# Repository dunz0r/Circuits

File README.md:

My collection libs, schematics, pcbs
Some done by me, some done by others

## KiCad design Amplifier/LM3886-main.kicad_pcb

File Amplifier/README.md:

An LM3886-powered gain-clone-amp

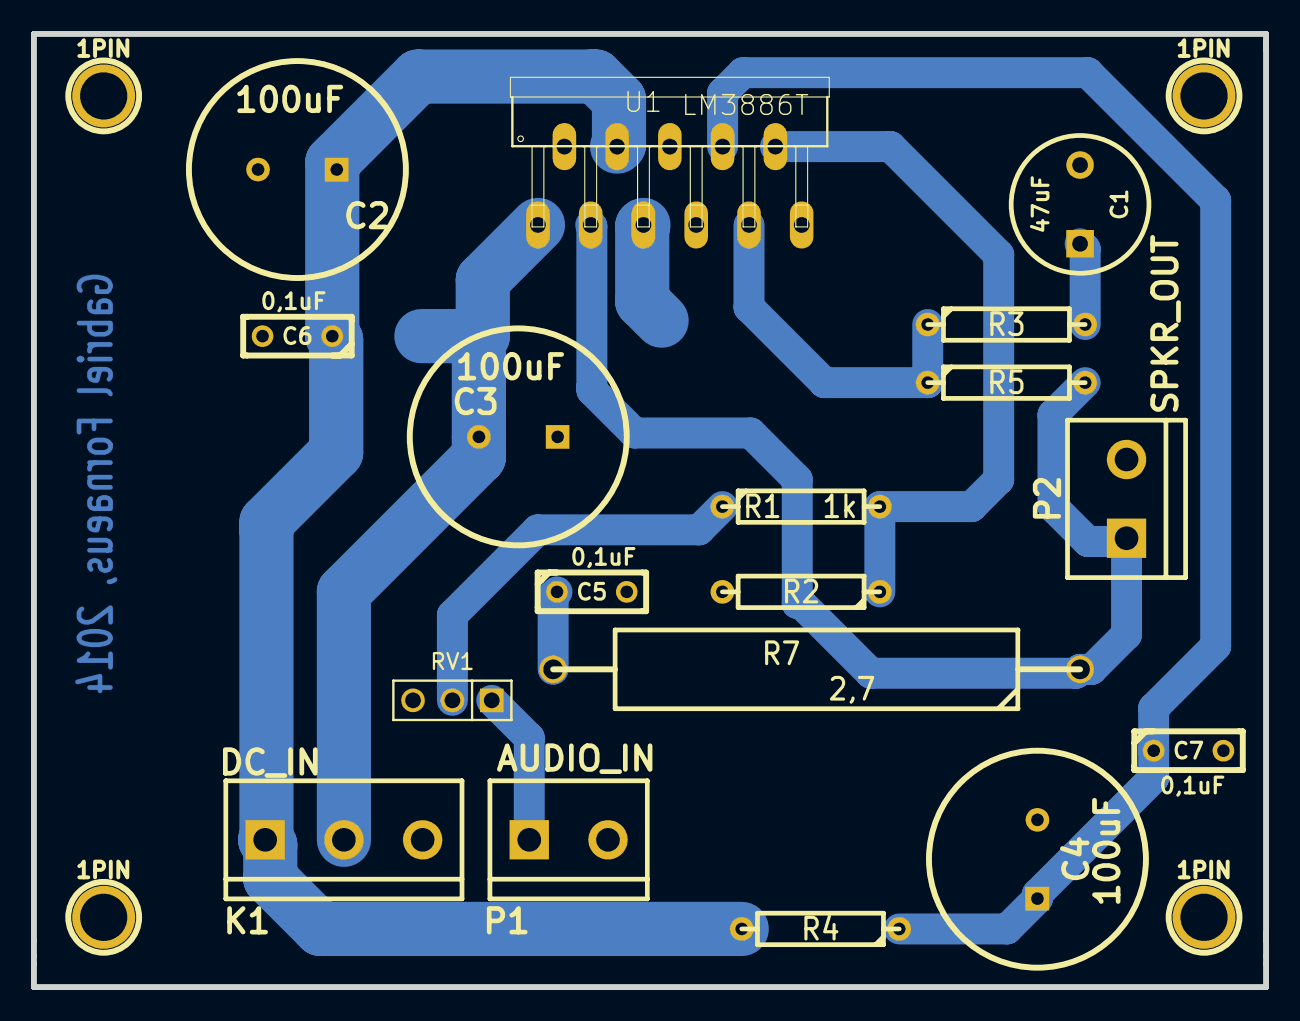
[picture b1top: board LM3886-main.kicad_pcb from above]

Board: 2 copper layers, 79.5 x 61.5 mm, 22 parts (0 on the bottom side), 11 nets.

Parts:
1PIN, 1PIN#2, 1PIN#3, 1PIN#4: P***; 1pin
C1: 47uF; C2V8
C2, C3, C4: 100uF; CP
C5, C6, C7: 0,1uF; C3
K1: DC_IN; bornier3
P1: AUDIO_IN; bornier2
P2: SPKR_OUT; bornier2
R1: 1k; R4
R2, R5: 22k; R4
R3: 680; R4
R4: 10k; R4
R7: 2,7; R8
RV1: 10k; PIN_ARRAY_3X1
U1: LM3886T; lmopamp-LM3886

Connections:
GND: C1.2, C2.1, C3.2, C4.1, C5.2, C6.2, C7.2, K1.3, P1.2, P2.2, R2.2, RV1.3, U1.7
unnamed: R1.2, R2.1, U1.10
unnamed: C1.1, R3.2
unnamed: C4.2, C7.1, R4.1, U1.8
unnamed: R1.1, RV1.2
unnamed: P1.1, RV1.1
unnamed: R3.1, R5.1, U1.9
unnamed: C5.1, R7.2
unnamed: P2.1, R5.2, R7.1, U1.3
VCC: C3.1, K1.2, U1.1, U1.5
VEE: C2.2, C6.1, K1.1, R4.2, U1.4

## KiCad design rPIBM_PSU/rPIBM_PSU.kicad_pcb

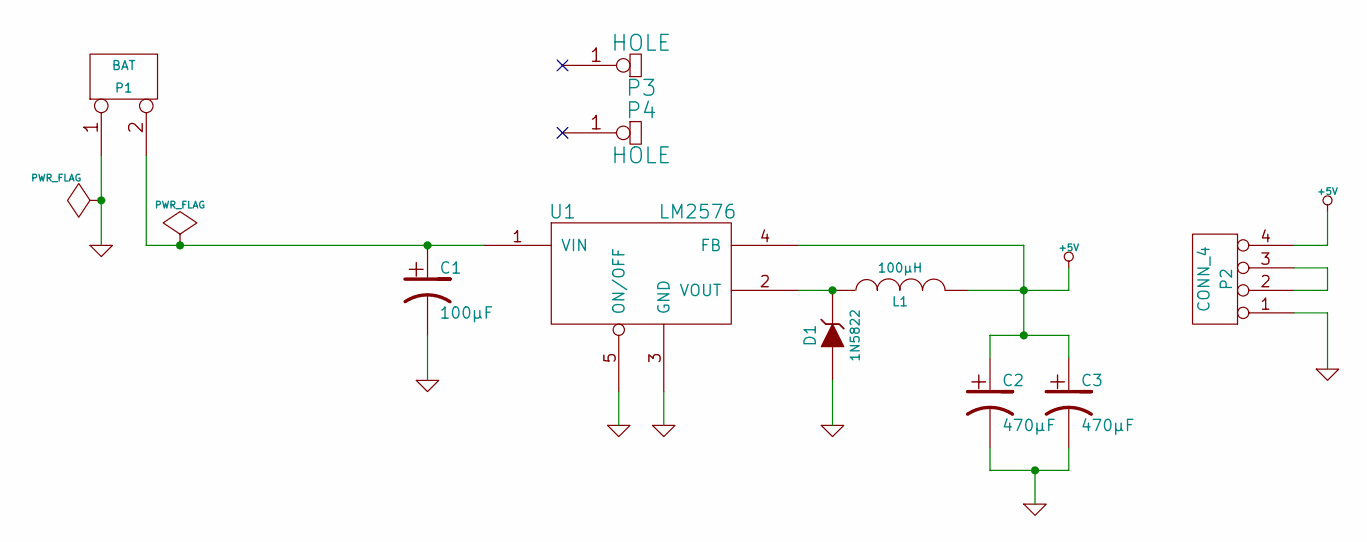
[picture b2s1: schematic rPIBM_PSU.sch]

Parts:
C1: 100µF
C2, C3: 470µF
D1: 1N5822
L1: 100µH
P1: BAT
P2: CONN_4
P3, P4: HOLE
U1: LM2576

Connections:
+5V: C2.1, C3.1, L1.2, P2.4, U1.4 (FB)
GND: C1.2, C2.2, C3.2, D1.1 (A), P1.1, P2.1, U1.3 (GND), U1.5 (ON/OFF)
unnamed: P2.2, P2.3
unnamed: D1.2 (K), L1.1, U1.2 (VOUT)
unnamed: C1.1, P1.2 (PM), U1.1 (VIN)

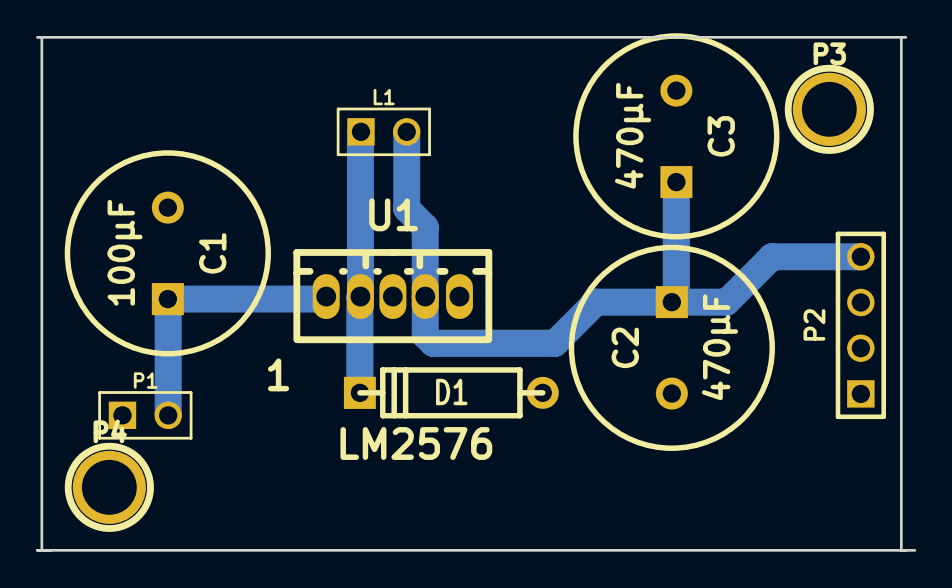
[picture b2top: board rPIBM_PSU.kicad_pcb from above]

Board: 2 copper layers, 48.8 x 28.5 mm, 10 parts (0 on the bottom side), 5 nets.

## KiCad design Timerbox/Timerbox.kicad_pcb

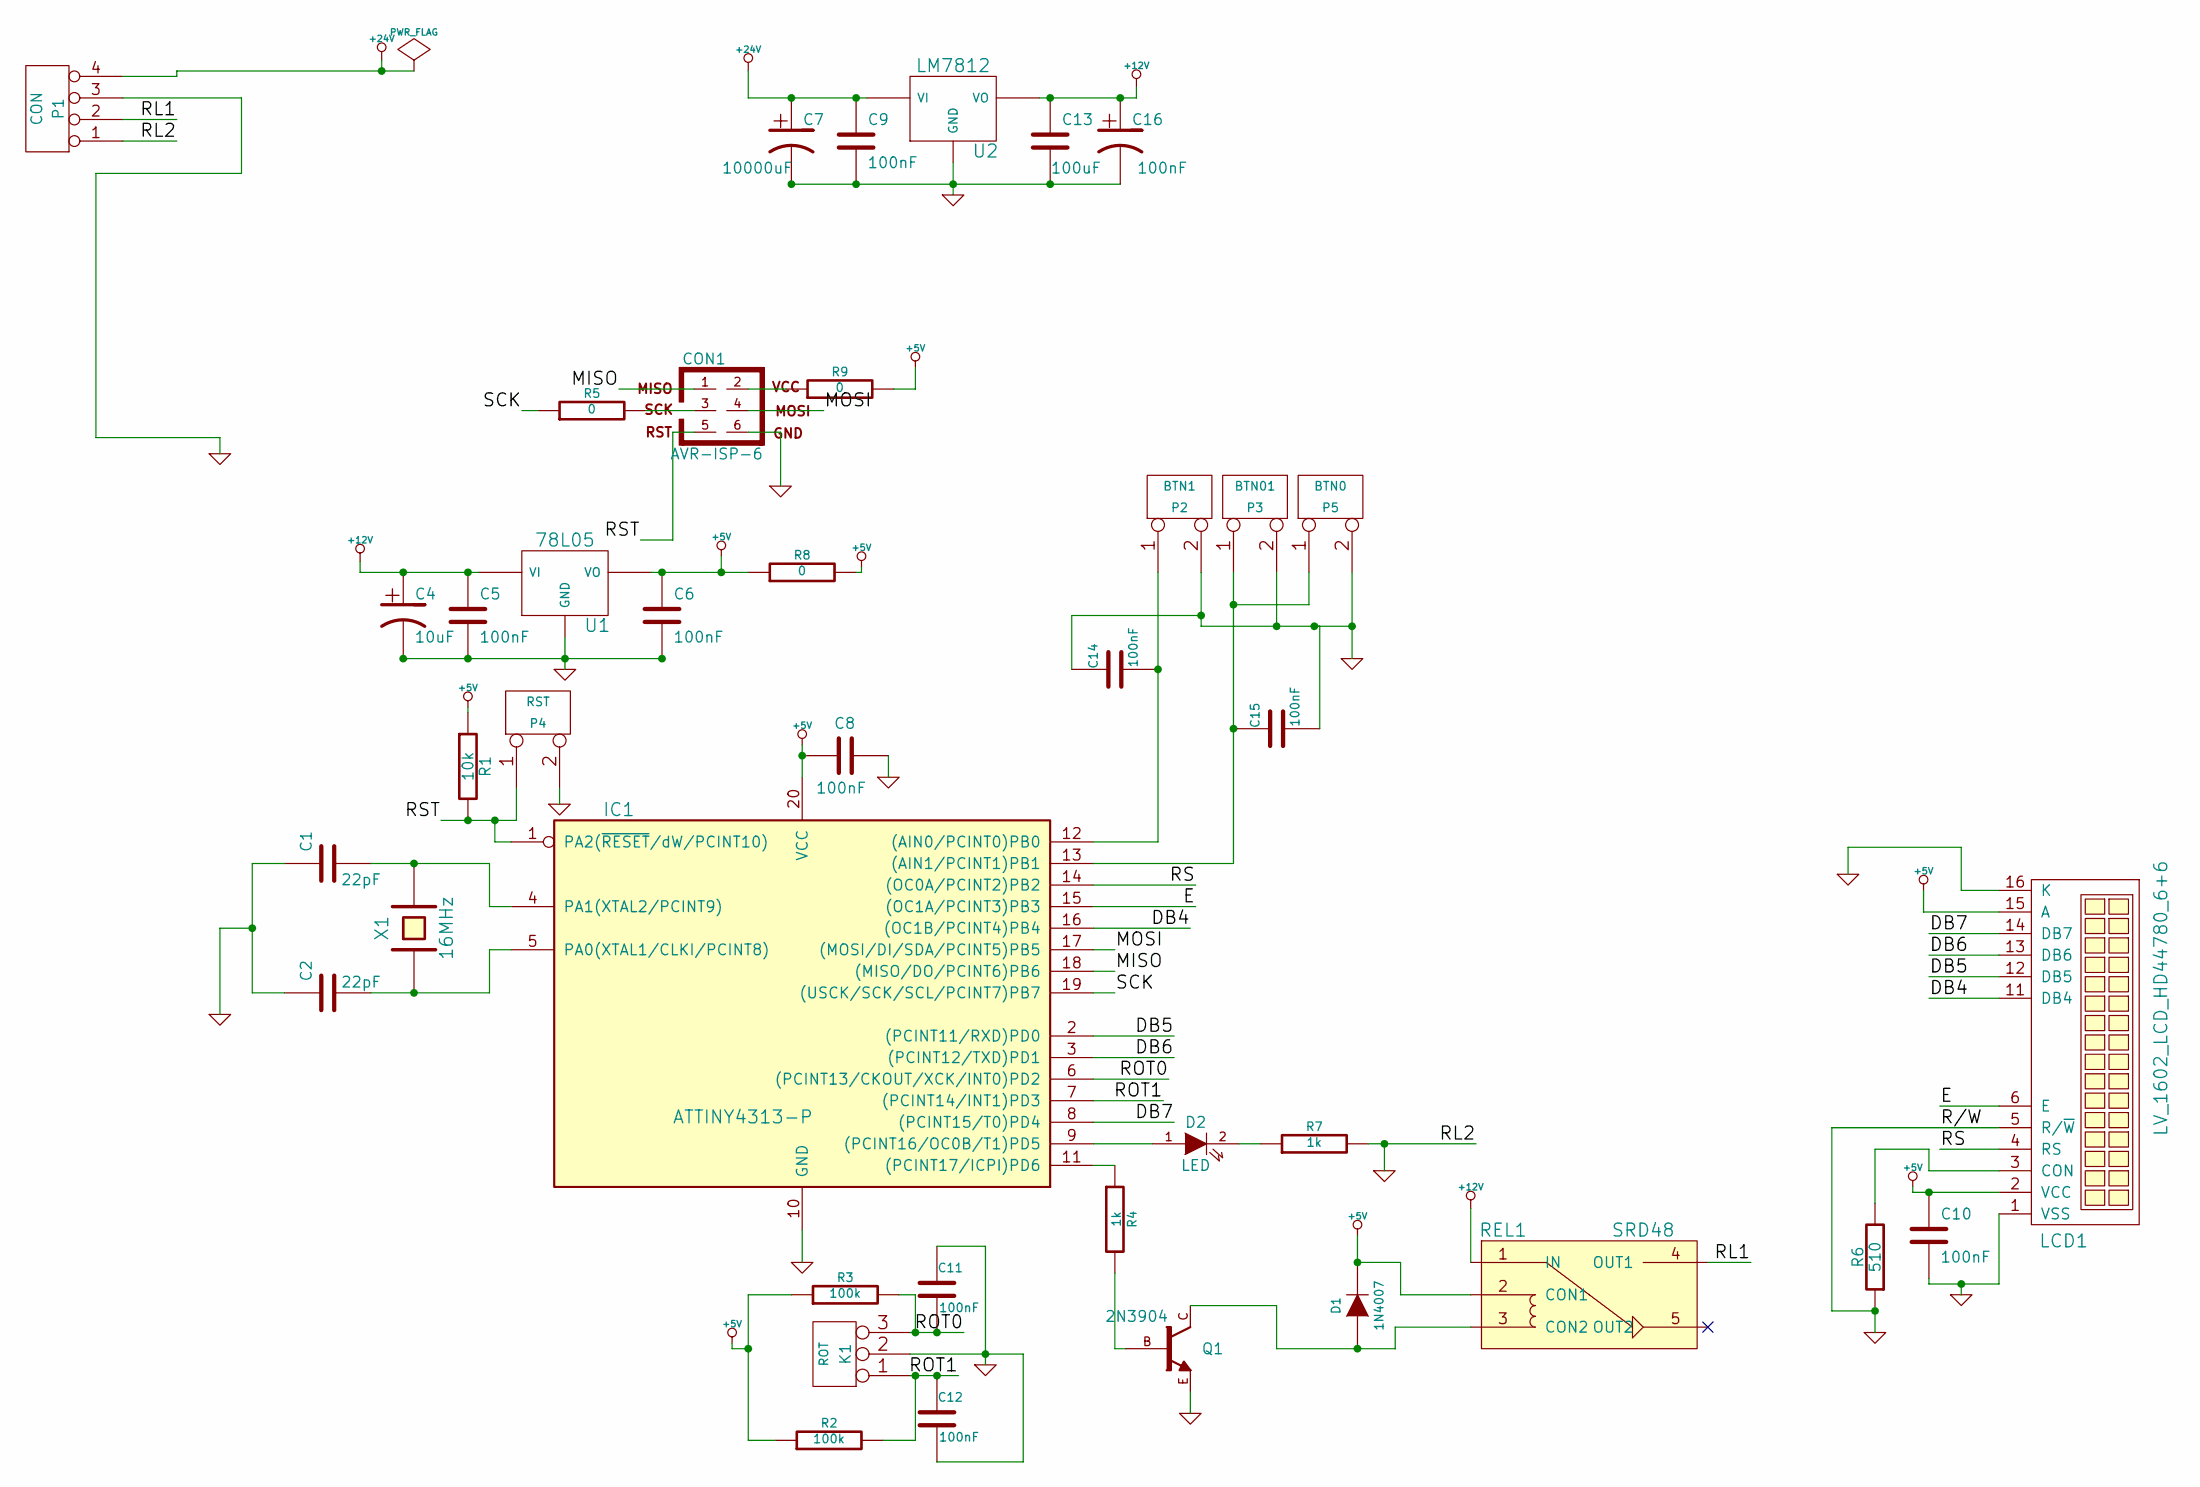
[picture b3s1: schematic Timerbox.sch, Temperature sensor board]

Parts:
C1, C2: 22pF
C4: 10uF
C5, C6, C8, C9, C10, C13: 100nF
C7: 10000uF
C11, C12, C14, C15: 100nF
C16: 100uF
CON1: AVR-ISP-6
D1: 1N4007
D2: LED
IC1: ATTINY4313-P; DIP20
K1: ROT
LCD1: LV_1602_LCD_HD44780_6+6
P1: CON
P2: BTN1
P3: BTN01
P4: RST
P5: BTN0
Q1: 2N3904
R1: 10k
R2, R3: 100k
R4, R7: 1k
R5, R8, R9: 0
R6: 510
REL1: SRD48
U1: 78L05
U2: LM7812
X1: 16MHz

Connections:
+5V: C6.1, C8.1, C10.1, D1.2 (K), IC1.20 (VCC), LCD1.2 (VCC), LCD1.15 (A), R1.1, R2.1, R3.1, R8.1, R8.2, R9.2, REL1.2 (CON1), U1.VO
+12V: C4.1, C5.1, C13.1, C16.1, REL1.1 (IN), U1.VI, U2.VO
+24V: C7.1, C9.1, P1.4, U2.VI
/DB4: IC1.16 ((OC1B/PCINT4)PB4), LCD1.11 (DB4)
/DB5: IC1.2 ((PCINT11/RXD)PD0), LCD1.12 (DB5)
/DB6: IC1.3 ((PCINT12/TXD)PD1), LCD1.13 (DB6)
/DB7: IC1.8 ((PCINT15/T0)PD4), LCD1.14 (DB7)
/E: IC1.15 ((OC1A/PCINT3)PB3), LCD1.6 (E)
/MISO: CON1.1, IC1.18 ((MISO/DO/PCINT6)PB6)
/MOSI: CON1.4, IC1.17 ((MOSI/DI/SDA/PCINT5)PB5)
/RL1: P1.2, REL1.4 (OUT1)
/ROT0: C11.2, IC1.6 ((PCINT13/CKOUT/XCK/INT0)PD2), K1.3, R3.2
/ROT1: C12.1, IC1.7 ((PCINT14/INT1)PD3), K1.1, R2.2
/RS: IC1.14 ((OC0A/PCINT2)PB2), LCD1.4 (RS)
/RST: CON1.5, IC1.1 (PA2(~RESET~/dW/PCINT10)), P4.1, R1.2
/SCK: IC1.19 ((USCK/SCK/SCL/PCINT7)PB7), R5.1
GND: C1.1, C2.1, C4.2, C5.2, C6.2, C7.2, C8.2, C9.2, C10.2, C11.1, C12.2, C13.2, C14.1, C15.2, C16.2, CON1.6, IC1.10 (GND), K1.2 (PM), LCD1.1 (VSS), LCD1.5 (R/~W), LCD1.16 (K), P1.1, P1.3, P2.2 (PM), P3.2 (PM), P4.2 (PM), P5.2 (PM), Q1.E, R6.1, R7.2, U1.GND, U2.GND
unnamed: CON1.2, R9.1
unnamed: LCD1.3 (CON), R6.2
unnamed: CON1.3, R5.2
unnamed: Q1.B, R4.2
unnamed: IC1.11 ((PCINT17/ICPI)PD6), R4.1
unnamed: D2.2 (K), R7.1
unnamed: D2.1 (A), IC1.9 ((PCINT16/OC0B/T1)PD5)
unnamed: C1.2, IC1.4 (PA1(XTAL2/PCINT9)), X1.2
unnamed: C2.2, IC1.5 (PA0(XTAL1/CLKI/PCINT8)), X1.1
unnamed: C14.2, IC1.12 ((AIN0/PCINT0)PB0), P2.1
unnamed: C15.1, IC1.13 ((AIN1/PCINT1)PB1), P3.1, P5.1
unnamed: D1.1 (A), Q1.C, REL1.3 (CON2)

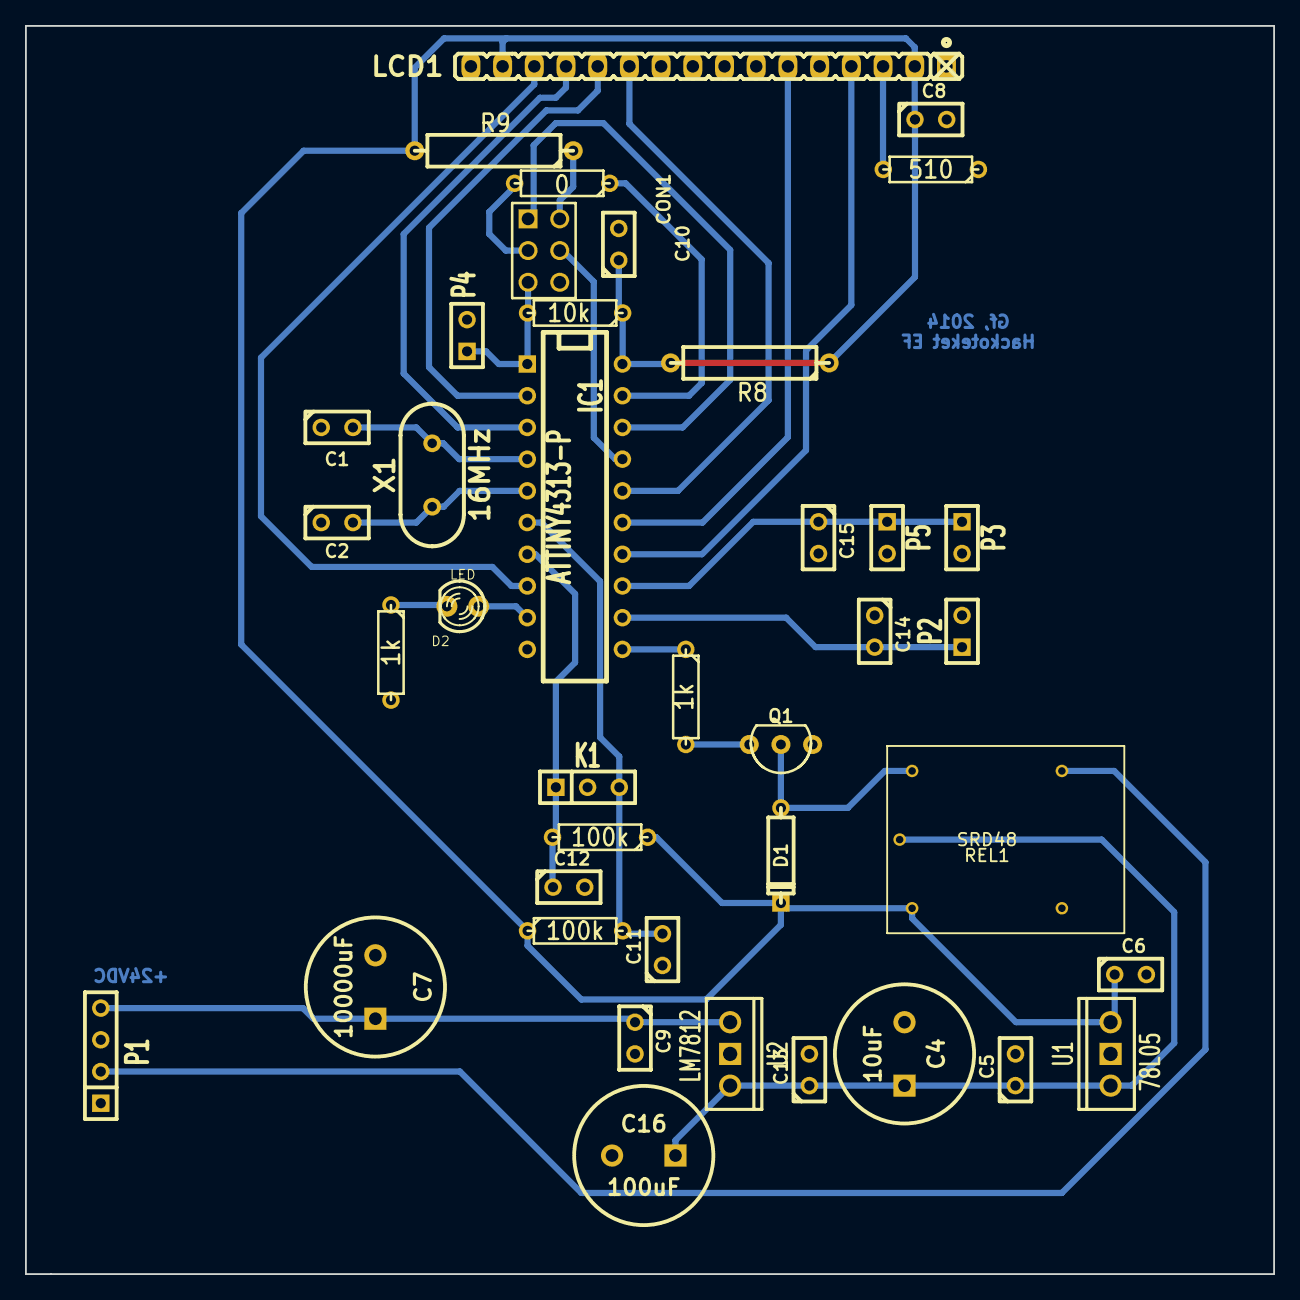
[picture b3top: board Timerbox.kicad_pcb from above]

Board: 2 copper layers, 100.0 x 100.0 mm, 40 parts (0 on the bottom side), 29 nets.

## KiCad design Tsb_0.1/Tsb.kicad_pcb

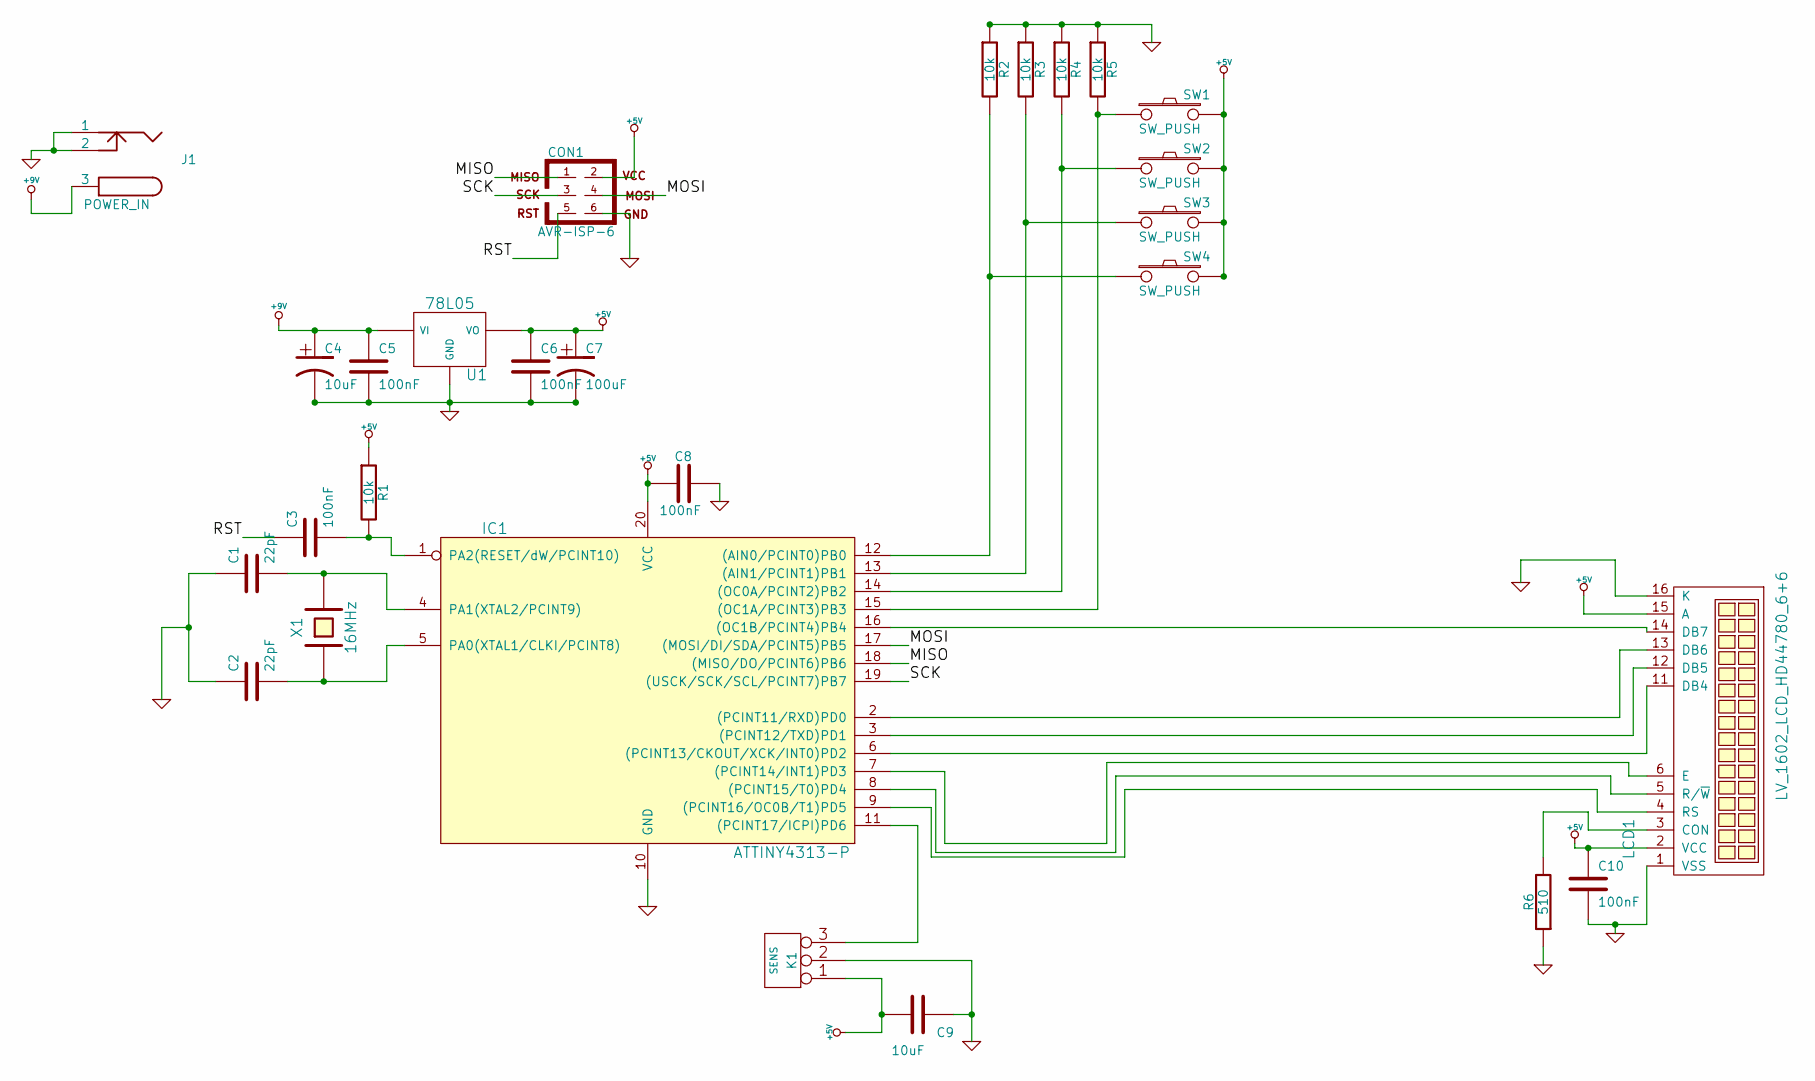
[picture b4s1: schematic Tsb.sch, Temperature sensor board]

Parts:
C1, C2: 22pF
C3, C5, C6, C8, C10: 100nF
C4, C9: 10uF
C7: 100uF
CON1: AVR-ISP-6
IC1: ATTINY4313-P; DIP20
J1: POWER_IN
K1: SENS
LCD1: LV_1602_LCD_HD44780_6+6
R1, R2, R3, R4, R5: 10k
R6: 510
SW1, SW2, SW3, SW4: SW_PUSH
U1: 78L05
X1: 16MHz

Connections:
+5V: C6.1, C7.1, C8.1, C9.2, C10.1, CON1.2, IC1.20 (VCC), K1.1, LCD1.2 (VCC), LCD1.15 (A), R1.1, SW1.2, SW2.2, SW3.2, SW4.2, U1.VO
+9V: C4.1, C5.1, J1.3, U1.VI
/MISO: CON1.1, IC1.18 ((MISO/DO/PCINT6)PB6)
/MOSI: CON1.4, IC1.17 ((MOSI/DI/SDA/PCINT5)PB5)
/RST: C3.1, CON1.5
/SCK: CON1.3, IC1.19 ((USCK/SCK/SCL/PCINT7)PB7)
GND: C1.1, C2.1, C4.2, C5.2, C6.2, C7.2, C8.2, C9.1, C10.2, CON1.6, IC1.10 (GND), J1.1, J1.2, K1.2 (PM), LCD1.1 (VSS), LCD1.16 (K), R2.1, R3.1, R4.1, R5.1, R6.1, U1.GND
unnamed: IC1.11 ((PCINT17/ICPI)PD6), K1.3
unnamed: LCD1.3 (CON), R6.2
unnamed: IC1.12 ((AIN0/PCINT0)PB0), R2.2, SW4.1
unnamed: IC1.13 ((AIN1/PCINT1)PB1), R3.2, SW3.1
unnamed: IC1.14 ((OC0A/PCINT2)PB2), R4.2, SW2.1
unnamed: IC1.15 ((OC1A/PCINT3)PB3), R5.2, SW1.1
unnamed: IC1.8 ((PCINT15/T0)PD4), LCD1.5 (R/~W)
unnamed: IC1.7 ((PCINT14/INT1)PD3), LCD1.6 (E)
unnamed: IC1.9 ((PCINT16/OC0B/T1)PD5), LCD1.4 (RS)
unnamed: IC1.2 ((PCINT11/RXD)PD0), LCD1.13 (DB6)
unnamed: IC1.16 ((OC1B/PCINT4)PB4), LCD1.14 (DB7)
unnamed: IC1.3 ((PCINT12/TXD)PD1), LCD1.12 (DB5)
unnamed: IC1.6 ((PCINT13/CKOUT/XCK/INT0)PD2), LCD1.11 (DB4)
unnamed: C2.2, IC1.5 (PA0(XTAL1/CLKI/PCINT8)), X1.1
unnamed: C1.2, IC1.4 (PA1(XTAL2/PCINT9)), X1.2
unnamed: C3.2, IC1.1 (PA2(RESET/dW/PCINT10)), R1.2

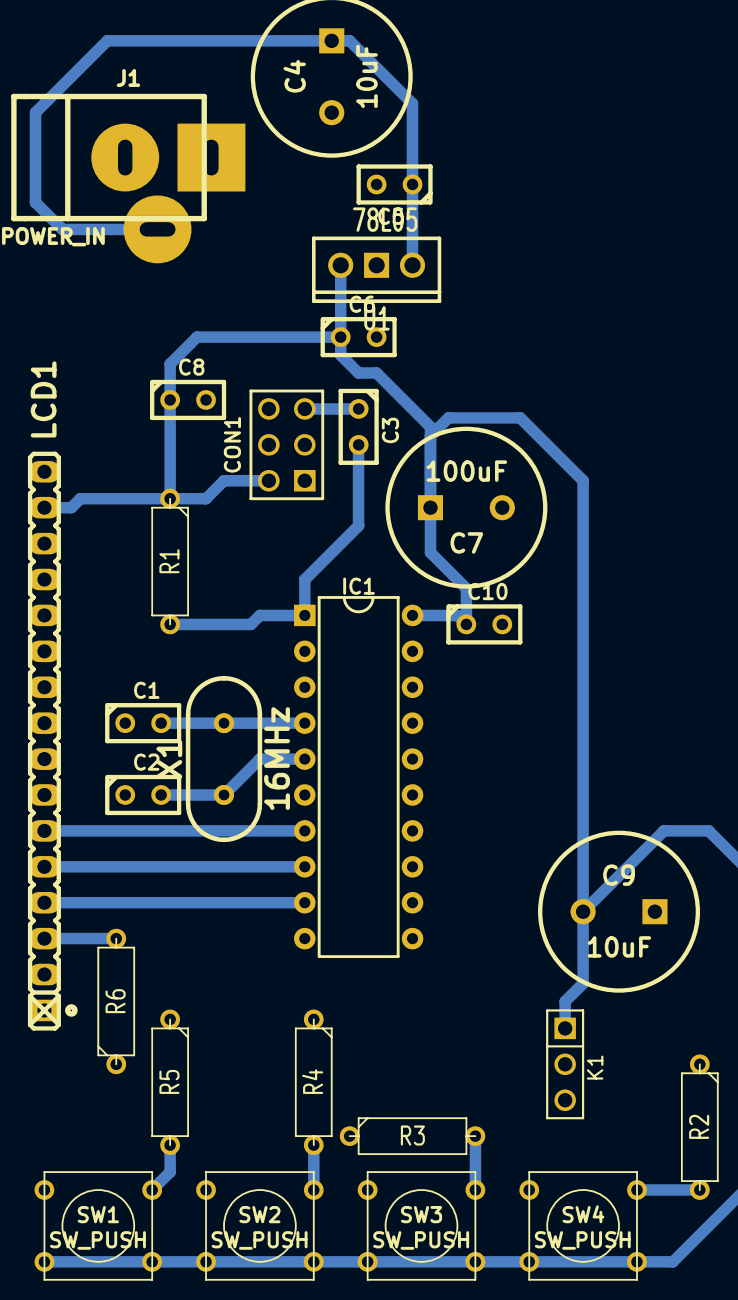
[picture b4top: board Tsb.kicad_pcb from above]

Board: 2 copper layers, 27 parts (0 on the bottom side), 23 nets.

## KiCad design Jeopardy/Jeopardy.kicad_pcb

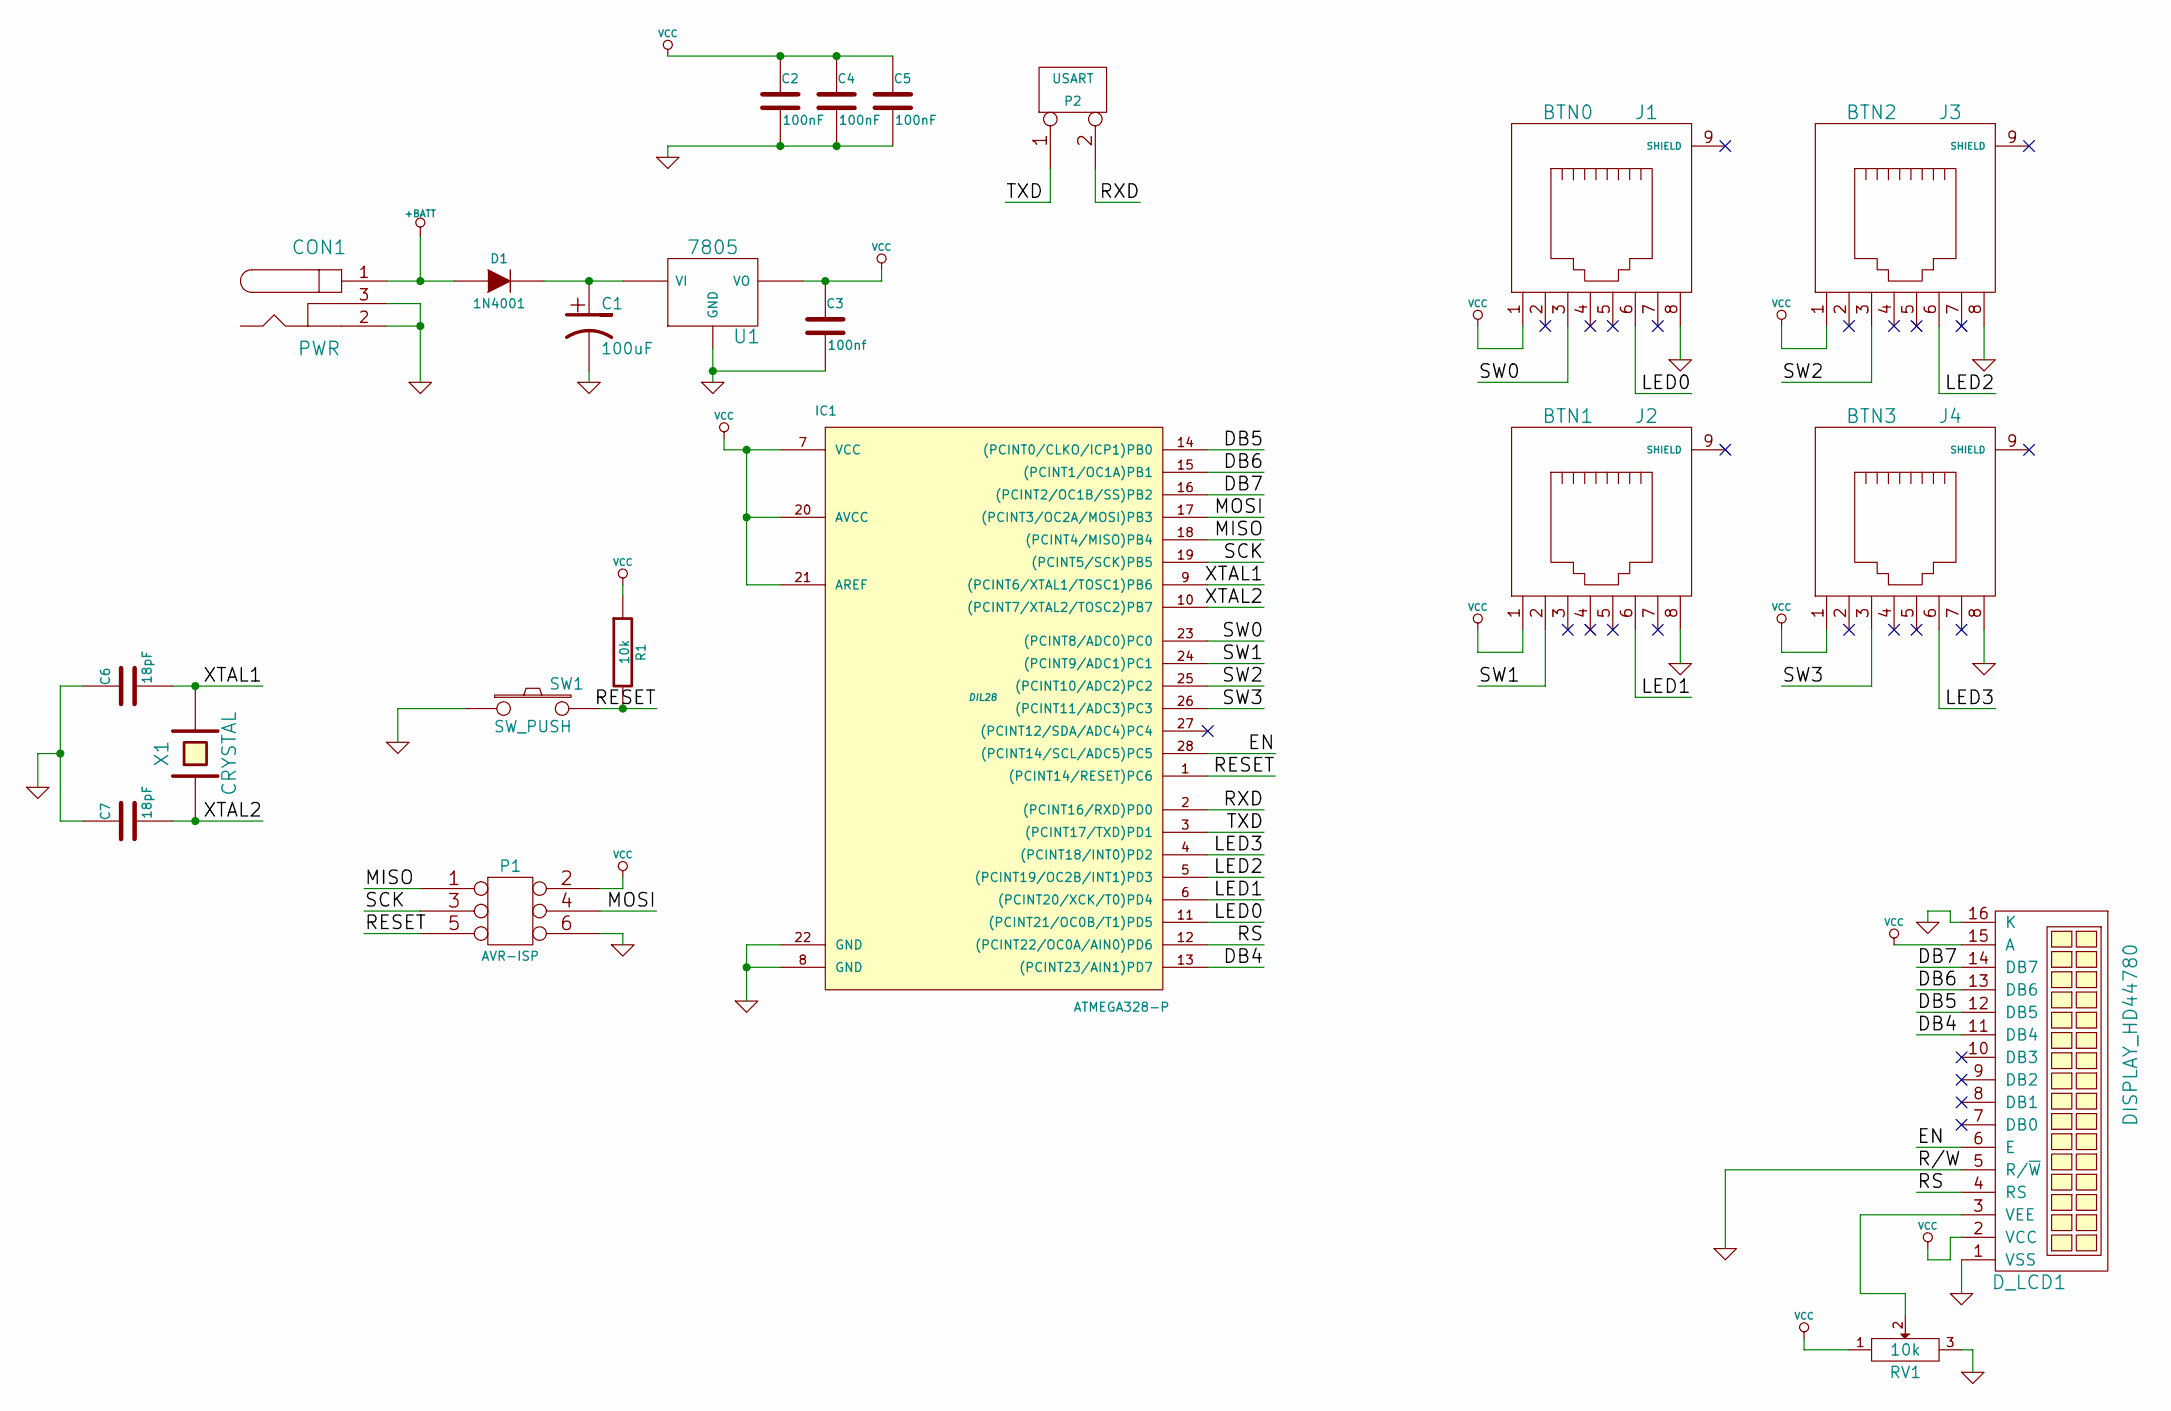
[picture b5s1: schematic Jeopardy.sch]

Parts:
C1: 100uF
C2, C4, C5: 100nF
C3: 100nf
C6, C7: 18pF
CON1: PWR
D1: 1N4001
D_LCD1: DISPLAY_HD44780
IC1: ATMEGA328-P; DIL28
J1: BTN0
J2: BTN1
J3: BTN2
J4: BTN3
P1: AVR-ISP
P2: USART
R1: 10k
RV1: 10k
SW1: SW_PUSH
U1: 7805
X1: CRYSTAL

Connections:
+BATT: CON1.1, D1.1 (A)
/DB4: D_LCD1.11 (DB4), IC1.13 ((PCINT23/AIN1)PD7)
/DB5: D_LCD1.12 (DB5), IC1.14 ((PCINT0/CLKO/ICP1)PB0)
/DB6: D_LCD1.13 (DB6), IC1.15 ((PCINT1/OC1A)PB1)
/DB7: D_LCD1.14 (DB7), IC1.16 ((PCINT2/OC1B/SS)PB2)
/EN: D_LCD1.6 (E), IC1.28 ((PCINT14/SCL/ADC5)PC5)
/LED0: IC1.11 ((PCINT21/OC0B/T1)PD5), J1.6
/LED1: IC1.6 ((PCINT20/XCK/T0)PD4), J2.6
/LED2: IC1.5 ((PCINT19/OC2B/INT1)PD3), J3.6
/LED3: IC1.4 ((PCINT18/INT0)PD2), J4.6
/MISO: IC1.18 ((PCINT4/MISO)PB4), P1.1
/MOSI: IC1.17 ((PCINT3/OC2A/MOSI)PB3), P1.4
/RESET: IC1.1 ((PCINT14/RESET)PC6), P1.5, R1.2, SW1.2
/RS: D_LCD1.4 (RS), IC1.12 ((PCINT22/OC0A/AIN0)PD6)
/RXD: IC1.2 ((PCINT16/RXD)PD0), P2.2 (PM)
/SCK: IC1.19 ((PCINT5/SCK)PB5), P1.3
/SW0: IC1.23 ((PCINT8/ADC0)PC0), J1.3
/SW1: IC1.24 ((PCINT9/ADC1)PC1), J2.2
/SW2: IC1.25 ((PCINT10/ADC2)PC2), J3.3
/SW3: IC1.26 ((PCINT11/ADC3)PC3), J4.3
/TXD: IC1.3 ((PCINT17/TXD)PD1), P2.1
/XTAL1: C6.2, IC1.9 ((PCINT6/XTAL1/TOSC1)PB6), X1.2
/XTAL2: C7.2, IC1.10 ((PCINT7/XTAL2/TOSC2)PB7), X1.1
GND: C1.2, C2.2, C3.2, C4.2, C5.2, C6.1, C7.1, CON1.2, CON1.3, D_LCD1.1 (VSS), D_LCD1.5 (R/~W), D_LCD1.16 (K), IC1.8 (GND), IC1.22 (GND), J1.8, J2.8, J3.8, J4.8, P1.6, RV1.3, SW1.1, U1.GND
unnamed: D_LCD1.3 (VEE), RV1.2
unnamed: C1.1, D1.2 (K), U1.VI
VCC: C2.1, C3.1, C4.1, C5.1, D_LCD1.2 (VCC), D_LCD1.15 (A), IC1.7 (VCC), IC1.20 (AVCC), IC1.21 (AREF), J1.1, J2.1, J3.1, J4.1, P1.2, R1.1, RV1.1, U1.VO

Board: 2 copper layers, 22 parts (0 on the bottom side), 27 nets, no tracks yet.

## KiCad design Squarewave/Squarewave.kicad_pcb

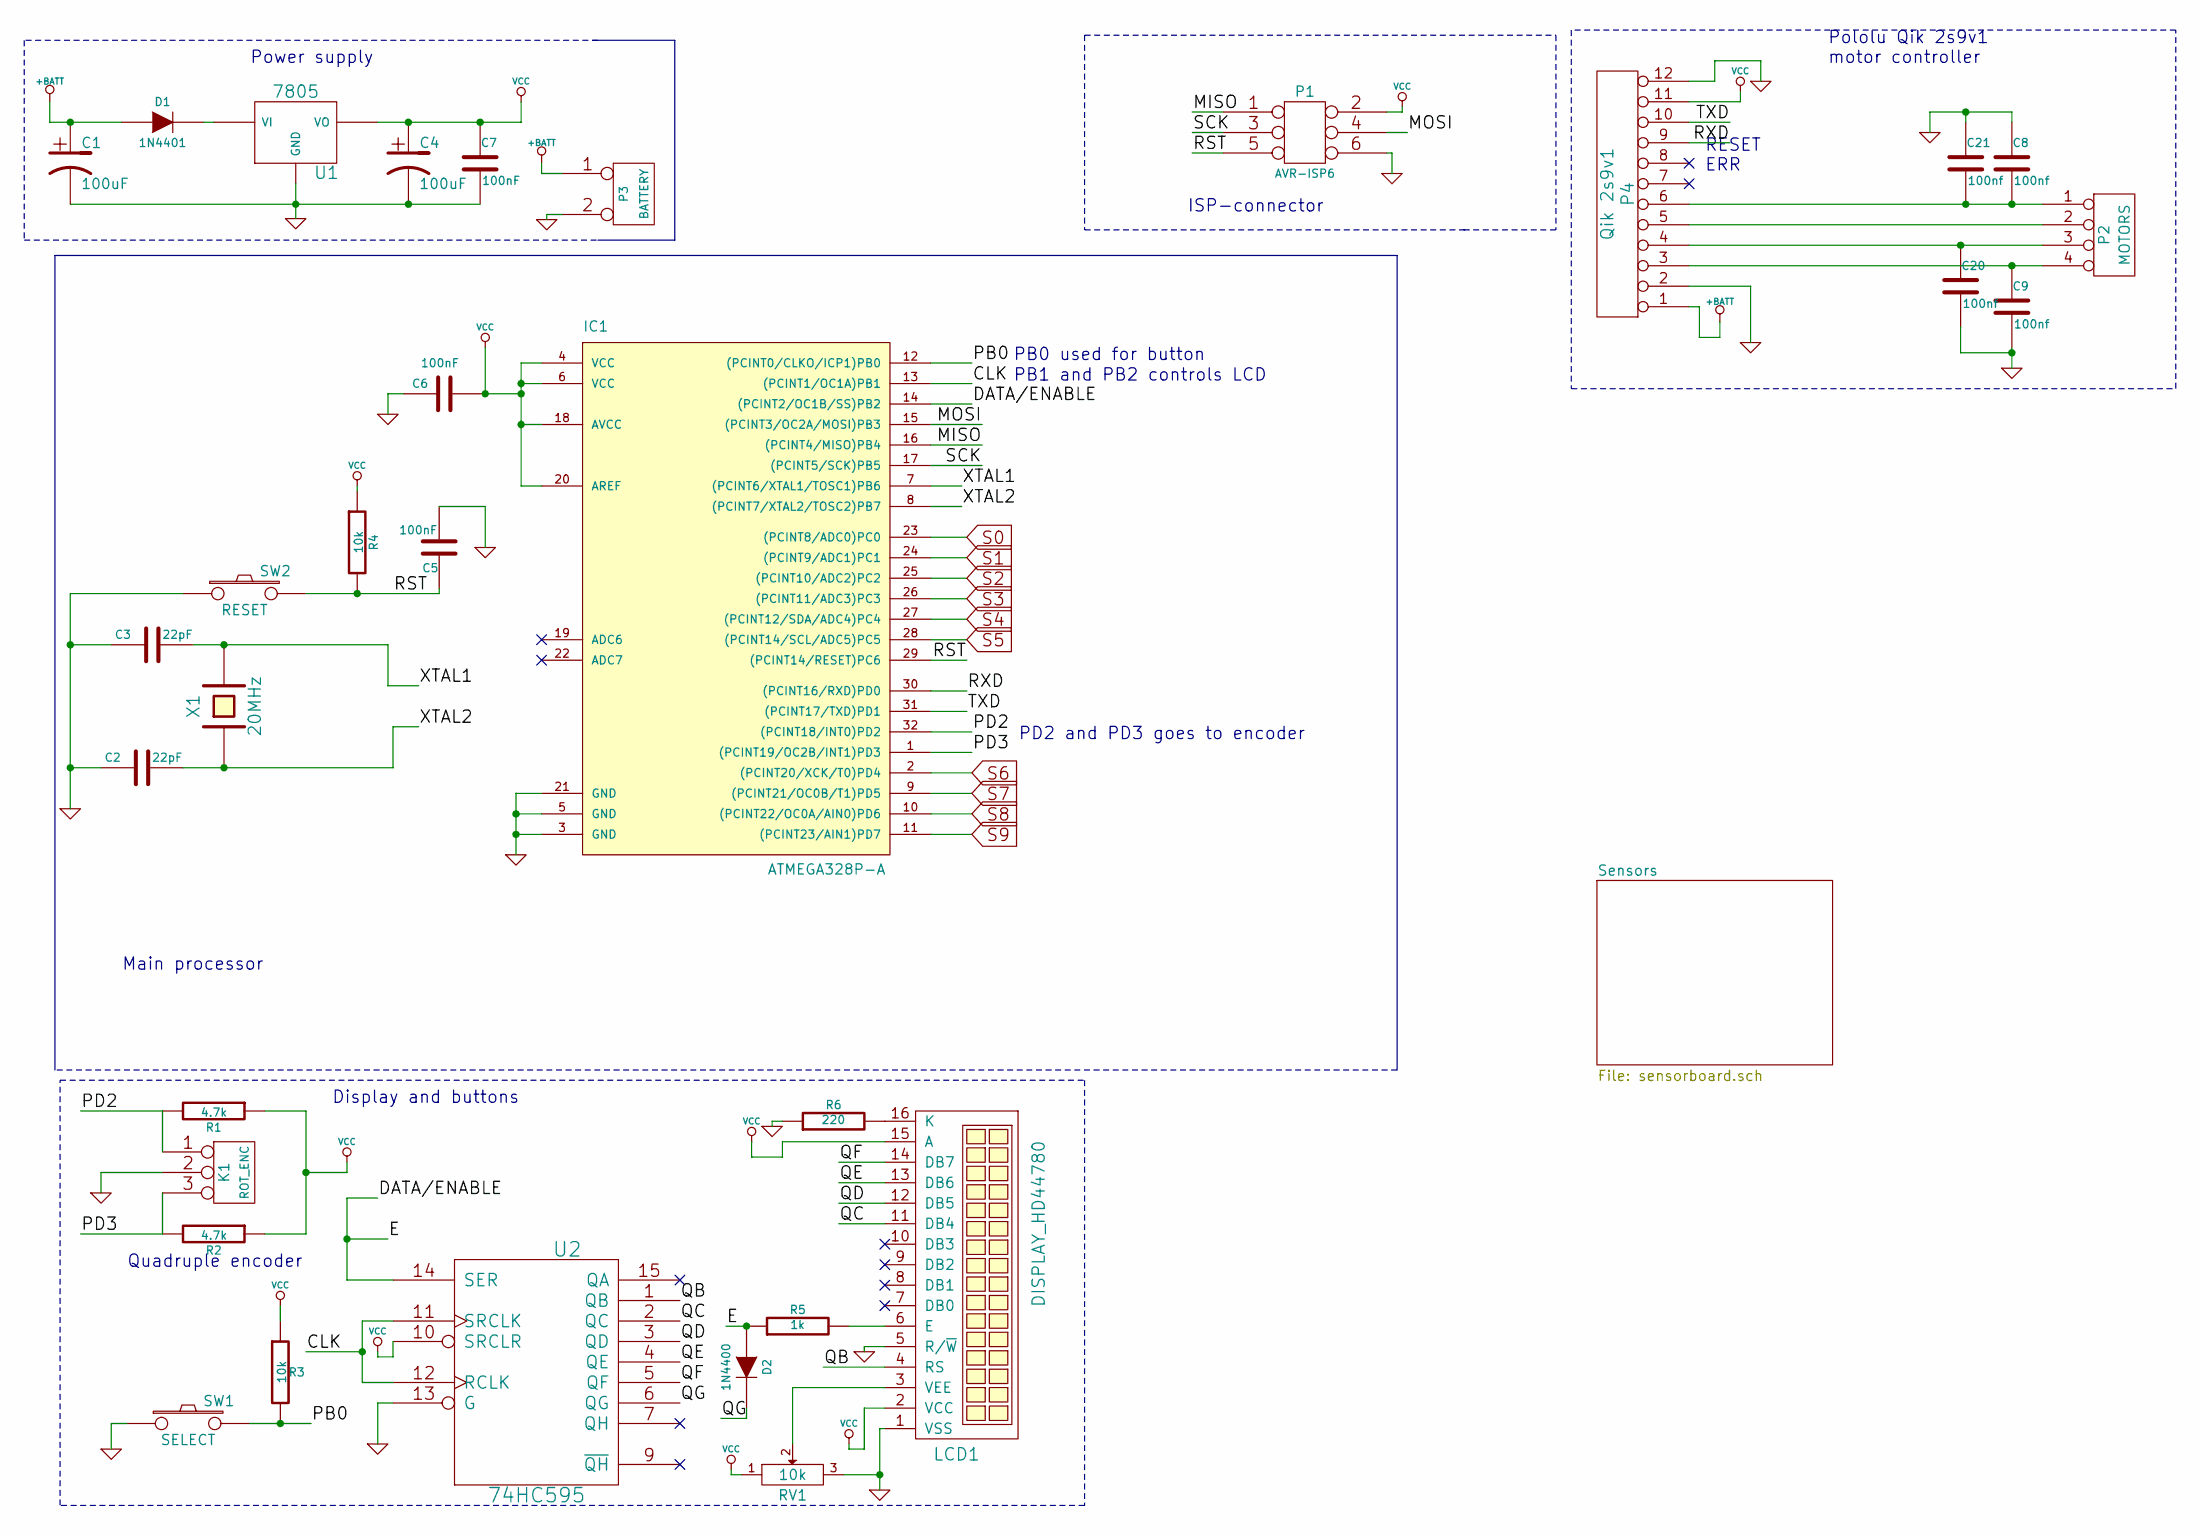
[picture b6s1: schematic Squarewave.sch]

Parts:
C1, C4: 100uF
C2, C3: 22pF
C5, C6, C7: 100nF
C8, C9, C20, C21: 100nf
D1: 1N4401
D2: 1N4400
IC1: ATMEGA328P-A; TQFP32
K1: ROT_ENC
LCD1: DISPLAY_HD44780
P1: AVR-ISP6
P2: MOTORS
P3: BATTERY
P4: Qik 2s9v1
R1, R2: 4.7k
R3, R4: 10k
R5: 1k
R6: 220
RV1: 10k
SW1: SELECT
SW2: RESET
U1: 7805
U2: 74HC595
X1: 20MHz

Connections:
+BATT: C1.1, D1.1 (A), P3.1, P4.1
/CLK: IC1.13 ((PCINT1/OC1A)PB1), U2.11 (SRCLK), U2.12 (RCLK)
/DATA/ENABLE: D2.1 (A), IC1.14 ((PCINT2/OC1B/SS)PB2), R5.1, U2.14 (SER)
/MISO: IC1.16 ((PCINT4/MISO)PB4), P1.1
/MOSI: IC1.15 ((PCINT3/OC2A/MOSI)PB3), P1.4
/PB0: IC1.12 ((PCINT0/CLKO/ICP1)PB0), R3.2, SW1.2
/PD2: IC1.32 ((PCINT18/INT0)PD2), K1.1, R1.2
/PD3: IC1.1 ((PCINT19/OC2B/INT1)PD3), K1.3, R2.2
/QB: LCD1.4 (RS), U2.1 (QB)
/QC: LCD1.11 (DB4), U2.2 (QC)
/QD: LCD1.12 (DB5), U2.3 (QD)
/QE: LCD1.13 (DB6), U2.4 (QE)
/QF: LCD1.14 (DB7), U2.5 (QF)
/QG: D2.2 (K), U2.6 (QG)
/RST: C5.1, IC1.29 ((PCINT14/RESET)PC6), P1.5, R4.2, SW2.2
/RXD: IC1.30 ((PCINT16/RXD)PD0), P4.9
/SCK: IC1.17 ((PCINT5/SCK)PB5), P1.3
/TXD: IC1.31 ((PCINT17/TXD)PD1), P4.10
/XTAL1: C3.2, IC1.7 ((PCINT6/XTAL1/TOSC1)PB6), X1.2
/XTAL2: C2.2, IC1.8 ((PCINT7/XTAL2/TOSC2)PB7), X1.1
GND: C1.2, C2.1, C3.1, C4.2, C5.2, C6.1, C7.2, C8.1, C9.2, C20.2, C21.1, IC1.3 (GND), IC1.5 (GND), IC1.21 (GND), K1.2 (PM), LCD1.1 (VSS), LCD1.5 (R/~W), P1.6, P3.2 (PM), P4.2, P4.12, R6.1, RV1.3, SW1.1, SW2.1, U1.GND, U2.8 (GND), U2.13 (G); also elsewhere on the board
unnamed: LCD1.6 (E), R5.2
unnamed: LCD1.3 (VEE), RV1.2
unnamed: D1.2 (K), U1.VI
unnamed: P2.2, P4.5
unnamed: C9.1, P2.4, P4.3
unnamed: C8.2, C21.2, P2.1, P4.6
unnamed: C20.1, P2.3, P4.4
unnamed: LCD1.16 (K), R6.2
S0: IC1.23 ((PCINT8/ADC0)PC0); also elsewhere on the board
S1: IC1.24 ((PCINT9/ADC1)PC1); also elsewhere on the board
S2: IC1.25 ((PCINT10/ADC2)PC2); also elsewhere on the board
S3: IC1.26 ((PCINT11/ADC3)PC3); also elsewhere on the board
S4: IC1.27 ((PCINT12/SDA/ADC4)PC4); also elsewhere on the board
S5: IC1.28 ((PCINT14/SCL/ADC5)PC5); also elsewhere on the board
S6: IC1.2 ((PCINT20/XCK/T0)PD4); also elsewhere on the board
S7: IC1.9 ((PCINT21/OC0B/T1)PD5); also elsewhere on the board
S8: IC1.10 ((PCINT22/OC0A/AIN0)PD6); also elsewhere on the board
S9: IC1.11 ((PCINT23/AIN1)PD7); also elsewhere on the board
VCC: C4.1, C6.2, C7.1, IC1.4 (VCC), IC1.6 (VCC), IC1.18 (AVCC), IC1.20 (AREF), LCD1.2 (VCC), LCD1.15 (A), P1.2, P4.11, R1.1, R2.1, R3.1, R4.1, RV1.1, U1.VO, U2.10 (SRCLR), U2.16 (VCC); also elsewhere on the board

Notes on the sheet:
PD2 and PD3 goes to encoder
Quadruple encoder
Power supply
Main processor
ISP-connector
Display and buttons
PB0 used for button
PB1 and PB2 controls LCD
Pololu Qik 2s9v1 motor controller
RESET ERR
